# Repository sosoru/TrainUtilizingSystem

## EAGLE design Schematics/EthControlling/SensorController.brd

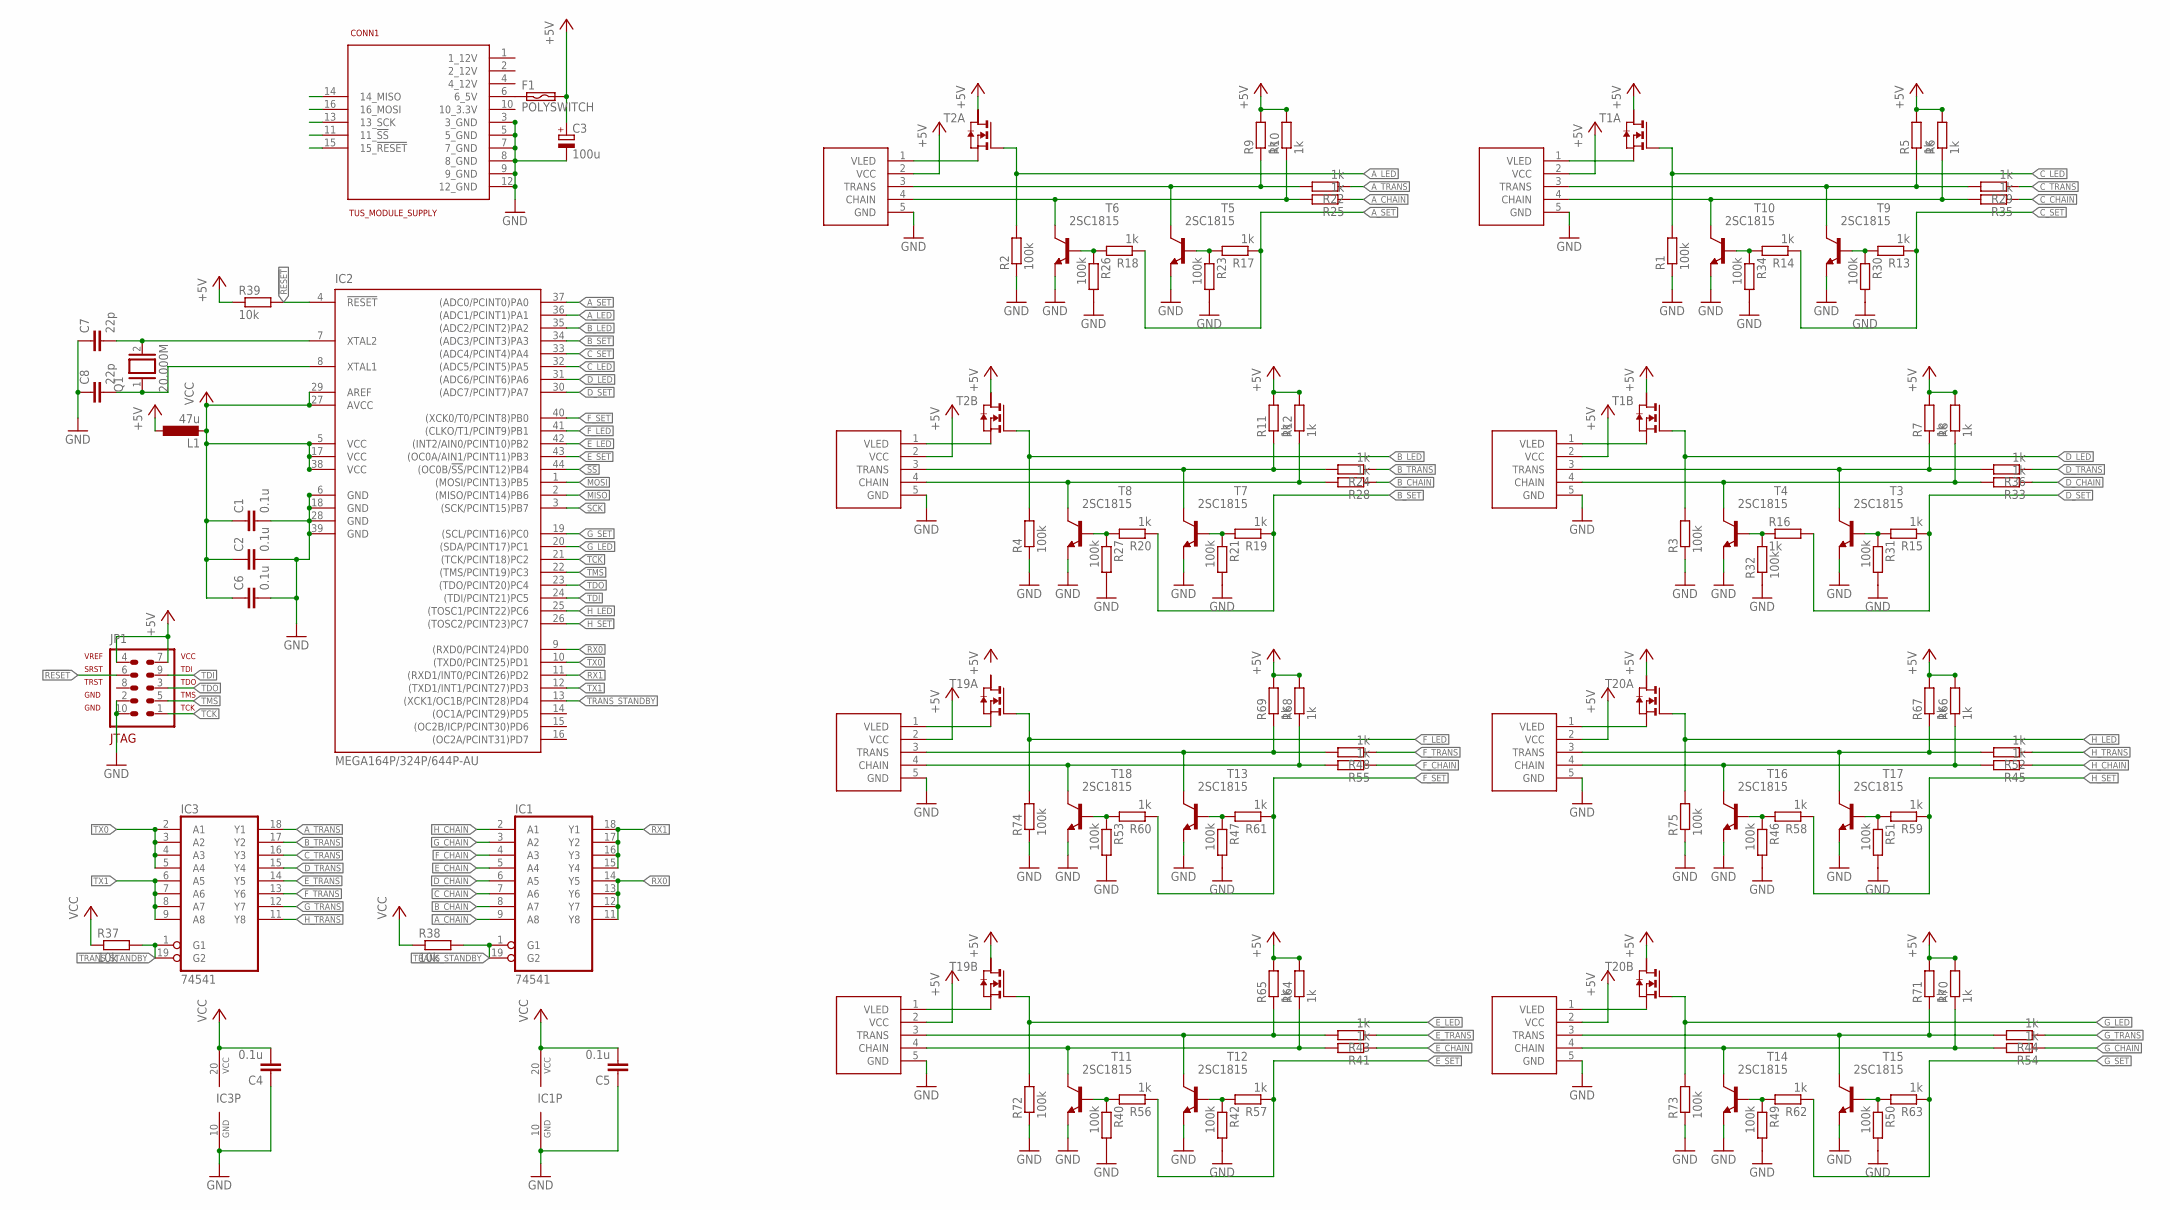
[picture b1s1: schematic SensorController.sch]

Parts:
A_OUT: SERIAL_SENSORXH; XH-5
B_OUT: SERIAL_SENSORXH; XH-5
C1, C2, C4, C5, C6: 0.1u; C1608
C3: 100u; E2,5-7
C7, C8: 22p; C1608
CONN1: TUS_MODULE_SUPPLY; 2X08
C_OUT: SERIAL_SENSORXH; XH-5
D_OUT: SERIAL_SENSORXH; XH-5
E_OUT: SERIAL_SENSORXH; XH-5
F1: POLYSWITCH; 0207/2V
F_OUT: SERIAL_SENSORXH; XH-5
G_OUT: SERIAL_SENSORXH; XH-5
H_OUT: SERIAL_SENSORXH; XH-5
IC1, IC3: 74541; SSOP20
IC2: MEGA164P/324P/644P-AU; TQFP44
JP1: AVR-JTAG-10
L1: 47u; L1812
Q1: 20.000M; QS
R1, R2, R3, R4, R21, R23, R26, R27, R30, R31, R32, R34, R40, R42, R46, R47, R49, R50, R51, R53, R72, R73, R74, R75: 100k; R0603
R5, R6, R7, R8, R9, R10, R11, R12, R13, R14, R15, R16, R17, R18, R19, R20, R22, R24, R25, R28, R29, R33, R35, R36, R41, R43, R44, R45, R48, R52, R54, R55, R56, R57, R58, R59, R60, R61, R62, R63, R64, R65, R66, R67, R68, R69, R70, R71: 1k; R0603
R37, R38, R39: 10k; R0603
T1, T2, T19, T20: NMOS2SO8; SO8
T3, T4, T5, T6, T7, T8, T9, T10, T11, T12, T13, T14, T15, T16, T17, T18: 2SC1815; TO92-ECB

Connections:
!RESET: CONN1.15 (15_!RESET), IC2.4 (!RESET), JP1.6, R39.2
!SS: CONN1.11 (11_!SS), IC2.44 ((OC0B/!SS!/PCINT12)PB4)
+5V: A_OUT.2 (VCC), B_OUT.2 (VCC), C3.+, C_OUT.2 (VCC), D_OUT.2 (VCC), E_OUT.2 (VCC), F1.2, F_OUT.2 (VCC), G_OUT.2 (VCC), H_OUT.2 (VCC), JP1.4, JP1.7, L1.1, R5.2, R6.2, R7.2, R8.2, R9.2, R10.2, R11.2, R12.2, R39.1, R64.2, R65.2, R66.2, R67.2, R68.2, R69.2, R70.2, R71.2, T1.6 (D), T1.8 (D), T2.6 (D), T2.8 (D), T19.6 (D), T20.6 (D), T20.8 (D)
A_CHAIN: IC1.9 (A8), R25.1
A_LED: IC2.36 ((ADC1/PCINT1)PA1), R2.2, T2.2 (G)
A_SET: IC2.37 ((ADC0/PCINT0)PA0), R17.1, R18.1
A_TRANS: IC3.18 (Y1), R22.1
B_CHAIN: IC1.8 (A7), R28.1
B_LED: IC2.35 ((ADC2/PCINT2)PA2), R4.2, T2.4 (G)
B_SET: IC2.34 ((ADC3/PCINT3)PA3), R19.1, R20.1
B_TRANS: IC3.17 (Y2), R24.1
C_CHAIN: IC1.7 (A6), R35.1
C_LED: IC2.32 ((ADC5/PCINT5)PA5), R1.2, T1.2 (G)
C_SET: IC2.33 ((ADC4/PCINT4)PA4), R13.1, R14.1
C_TRANS: IC3.16 (Y3), R29.1
D_CHAIN: IC1.6 (A5), R33.1
D_LED: IC2.31 ((ADC6/PCINT6)PA6), R3.2, T1.4 (G)
D_SET: IC2.30 ((ADC7/PCINT7)PA7), R15.1, R16.2
D_TRANS: IC3.15 (Y4), R36.1
E_CHAIN: IC1.5 (A4), R41.1
E_LED: IC2.42 ((INT2/AIN0/PCINT10)PB2), R72.2, T19.4 (G)
E_SET: IC2.43 ((OC0A/AIN1/PCINT11)PB3), R56.1, R57.1
E_TRANS: IC3.14 (Y5), R43.1
F_CHAIN: IC1.4 (A3), R55.1
F_LED: IC2.41 ((CLKO/T1/PCINT9)PB1), R74.2, T19.2 (G)
F_SET: IC2.40 ((XCK0/T0/PCINT8)PB0), R60.1, R61.1
F_TRANS: IC3.13 (Y6), R48.1
GND: A_OUT.5 (GND), B_OUT.5 (GND), C1.2, C2.2, C3.-, C4.1, C5.1, C6.2, C7.1, C8.1, CONN1.3 (3_GND), CONN1.5 (5_GND), CONN1.7 (7_GND), CONN1.8 (8_GND), CONN1.9 (9_GND), CONN1.12 (12_GND), C_OUT.5 (GND), D_OUT.5 (GND), E_OUT.5 (GND), F_OUT.5 (GND), G_OUT.5 (GND), H_OUT.5 (GND), IC1.10 (GND), IC2.6 (GND), IC2.18 (GND), IC2.28 (GND), IC2.39 (GND), IC3.10 (GND), JP1.2, JP1.10, R1.1, R2.1, R3.1, R4.1, R21.2, R23.2, R26.2, R27.2, R30.2, R31.2, R32.1, R34.2, R40.2, R42.2, R46.2, R47.2, R49.2, R50.2, R51.2, R53.2, R72.1, R73.1, R74.1, R75.1, T3.E, T4.E, T5.E, T6.E, T7.E, T8.E, T9.E, T10.E, T11.E, T12.E, T13.E, T14.E, T15.E, T16.E, T17.E, T18.E
G_CHAIN: IC1.3 (A2), R54.1
G_LED: IC2.20 ((SDA/PCINT17)PC1), R73.2, T20.4 (G)
G_SET: IC2.19 ((SCL/PCINT16)PC0), R62.1, R63.1
G_TRANS: IC3.12 (Y7), R44.1
H_CHAIN: IC1.2 (A1), R45.1
H_LED: IC2.25 ((TOSC1/PCINT22)PC6), R75.2, T20.2 (G)
H_SET: IC2.26 ((TOSC2/PCINT23)PC7), R58.1, R59.1
H_TRANS: IC3.11 (Y8), R52.1
MISO: CONN1.14 (14_MISO), IC2.2 ((MISO/PCINT14)PB6)
MOSI: CONN1.16 (16_MOSI), IC2.1 ((MOSI/PCINT13)PB5)
unnamed: A_OUT.1 (VLED), T2.1 (S)
unnamed: C8.2, IC2.8 (XTAL1), Q1.1
unnamed: R17.2, R23.1, T5.B
unnamed: C7.2, IC2.7 (XTAL2), Q1.2
unnamed: R18.2, R26.1, T6.B
unnamed: B_OUT.1 (VLED), T2.3 (S)
unnamed: R19.2, R21.1, T7.B
unnamed: R20.2, R27.1, T8.B
unnamed: F_OUT.1 (VLED), T19.1 (S)
unnamed: R47.1, R61.2, T13.B
unnamed: R53.1, R60.2, T18.B
unnamed: E_OUT.1 (VLED), T19.3 (S)
unnamed: R42.1, R57.2, T12.B
unnamed: R40.1, R56.2, T11.B
unnamed: C_OUT.1 (VLED), T1.1 (S)
unnamed: R13.2, R30.1, T9.B
unnamed: R14.2, R34.1, T10.B
unnamed: D_OUT.1 (VLED), T1.3 (S)
unnamed: R15.2, R31.1, T3.B
unnamed: R16.1, R32.2, T4.B
unnamed: H_OUT.1 (VLED), T20.1 (S)
unnamed: R51.1, R59.2, T17.B
unnamed: R46.1, R58.2, T16.B
unnamed: G_OUT.1 (VLED), T20.3 (S)
unnamed: R50.1, R63.2, T15.B
unnamed: R49.1, R62.2, T14.B
unnamed: CONN1.6 (6_5V), F1.1
unnamed: A_OUT.3 (TRANS), R9.1, R22.2, T5.C
unnamed: B_OUT.3 (TRANS), R11.1, R24.2, T7.C
unnamed: C_OUT.3 (TRANS), R5.1, R29.2, T9.C
unnamed: D_OUT.3 (TRANS), R7.1, R36.2, T3.C
unnamed: F_OUT.3 (TRANS), R48.2, R69.1, T13.C
unnamed: H_OUT.3 (TRANS), R52.2, R67.1, T17.C
unnamed: E_OUT.3 (TRANS), R43.2, R65.1, T12.C
unnamed: G_OUT.3 (TRANS), R44.2, R71.1, T15.C
unnamed: A_OUT.4 (CHAIN), R10.1, R25.2, T6.C
unnamed: B_OUT.4 (CHAIN), R12.1, R28.2, T8.C
unnamed: F_OUT.4 (CHAIN), R55.2, R68.1, T18.C
unnamed: E_OUT.4 (CHAIN), R41.2, R64.1, T11.C
unnamed: D_OUT.4 (CHAIN), R8.1, R33.2, T4.C
unnamed: C_OUT.4 (CHAIN), R6.1, R35.2, T10.C
unnamed: H_OUT.4 (CHAIN), R45.2, R66.1, T16.C
unnamed: G_OUT.4 (CHAIN), R54.2, R70.1, T14.C
RX0: IC1.11 (Y8), IC1.12 (Y7), IC1.13 (Y6), IC1.14 (Y5), IC2.9 ((RXD0/PCINT24)PD0)
RX1: IC1.15 (Y4), IC1.16 (Y3), IC1.17 (Y2), IC1.18 (Y1), IC2.11 ((RXD1/INT0/PCINT26)PD2)
SCK: CONN1.13 (13_SCK), IC2.3 ((SCK/PCINT15)PB7)
TCK: IC2.21 ((TCK/PCINT18)PC2), JP1.1
TDI: IC2.24 ((TDI/PCINT21)PC5), JP1.9
TDO: IC2.23 ((TDO/PCINT20)PC4), JP1.3
TMS: IC2.22 ((TMS/PCINT19)PC3), JP1.5
TRANS_STANDBY: IC1.1 (G1), IC1.19 (G2), IC2.13 ((XCK1/OC1B/PCINT28)PD4), IC3.1 (G1), IC3.19 (G2), R37.2, R38.2
TX0: IC2.10 ((TXD0/PCINT25)PD1), IC3.2 (A1), IC3.3 (A2), IC3.4 (A3), IC3.5 (A4)
TX1: IC2.12 ((TXD1/INT1/PCINT27)PD3), IC3.6 (A5), IC3.7 (A6), IC3.8 (A7), IC3.9 (A8)
VCC: C1.1, C2.1, C4.2, C5.2, C6.1, IC1.20 (VCC), IC2.5 (VCC), IC2.17 (VCC), IC2.27 (AVCC), IC2.29 (AREF), IC2.38 (VCC), IC3.20 (VCC), L1.2, R37.1, R38.1

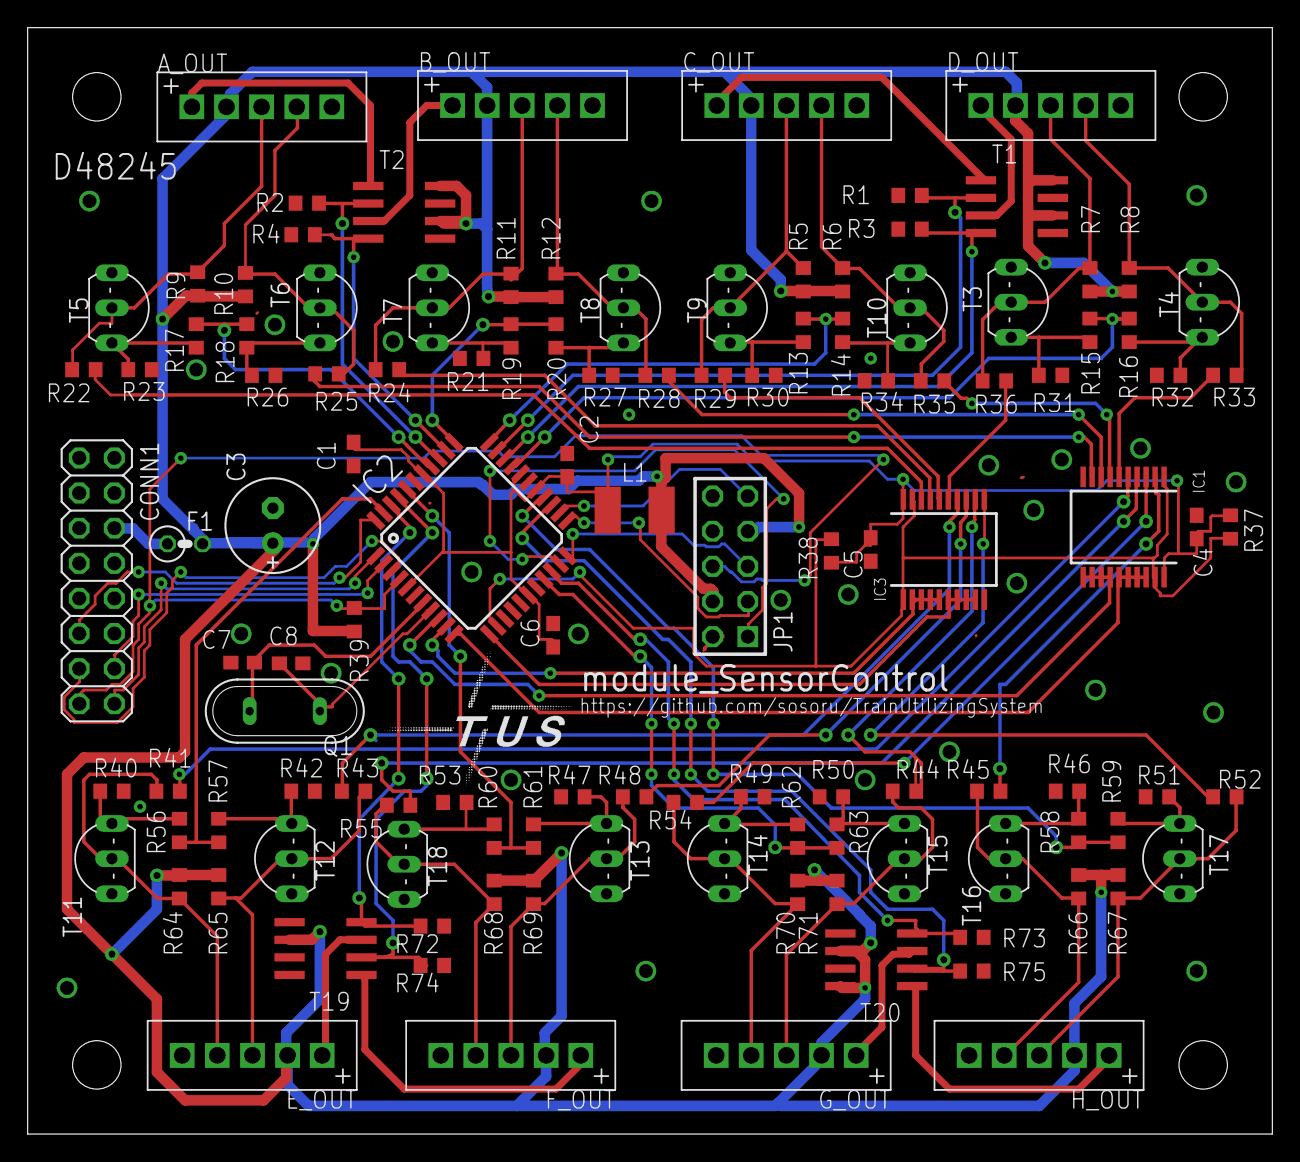
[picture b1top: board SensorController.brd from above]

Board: 2 copper layers, 90.0 x 80.0 mm, 119 parts (0 on the bottom side), 92 nets.

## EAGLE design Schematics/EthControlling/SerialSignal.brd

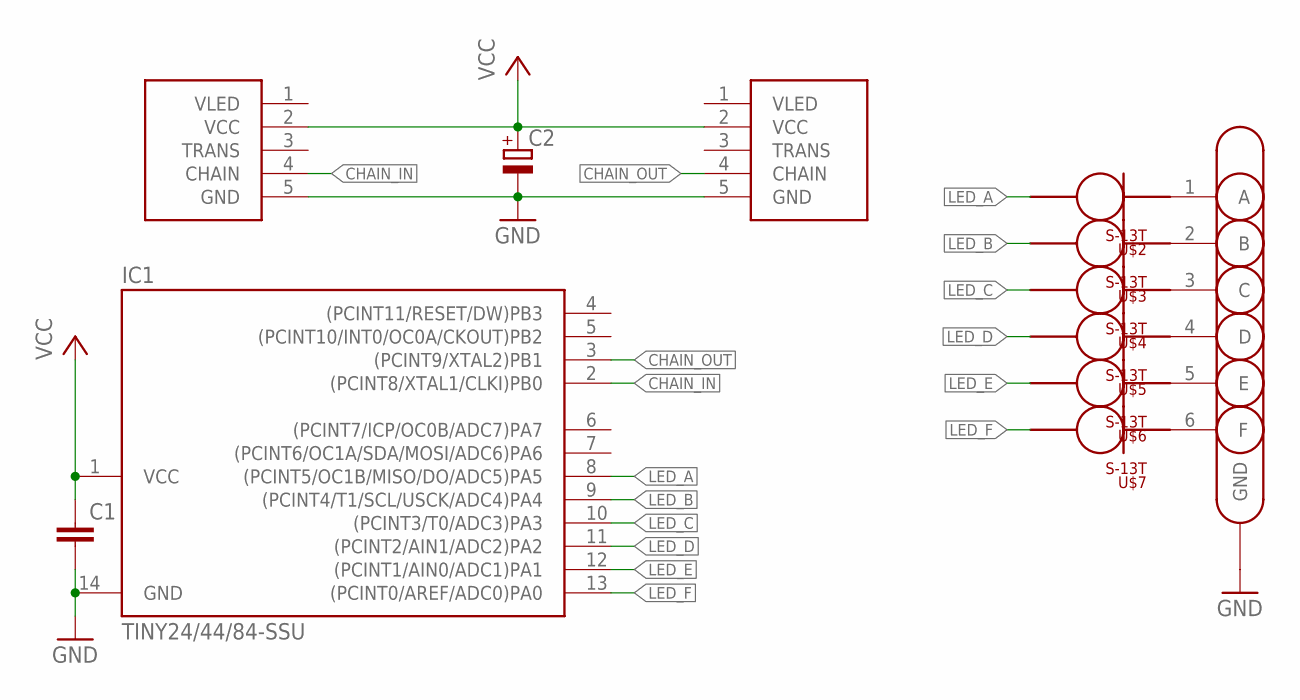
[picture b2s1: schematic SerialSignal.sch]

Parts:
C1: C-EUC0603; C0603
C2: CPOL-EUSMCC; SMC_C
IC1: TINY24/44/84-SSU; SOIC14
SMD1, SMD2: SERIAL_SENSOR; SERIAL_4
U$1: SIGNAL_CONNECTOR; SIGNEL_CONNECTOR
U$2, U$3, U$4, U$5, U$6, U$7: S-13T; S-1*3T

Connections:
CHAIN_IN: IC1.2 ((PCINT8/XTAL1/CLKI)PB0), SMD1.4 (CHAIN)
CHAIN_OUT: IC1.3 ((PCINT9/XTAL2)PB1), SMD2.4 (CHAIN)
GND: C1.2, C2.-, IC1.14 (GND), SMD1.5 (GND), SMD2.5 (GND), U$1.GND
LED_A: IC1.8 ((PCINT5/OC1B/MISO/DO/ADC5)PA5), U$2.A
LED_B: IC1.9 ((PCINT4/T1/SCL/USCK/ADC4)PA4), U$3.A
LED_C: IC1.10 ((PCINT3/T0/ADC3)PA3), U$4.A
LED_D: IC1.11 ((PCINT2/AIN1/ADC2)PA2), U$5.A
LED_E: IC1.12 ((PCINT1/AIN0/ADC1)PA1), U$6.A
LED_F: IC1.13 ((PCINT0/AREF/ADC0)PA0), U$7.A
unnamed: U$1.1 (A), U$2.C
unnamed: U$1.2 (B), U$3.C
unnamed: U$1.3 (C), U$4.C
unnamed: U$1.4 (D), U$5.C
unnamed: U$1.5 (E), U$6.C
unnamed: U$1.6 (F), U$7.C
VCC: C1.1, C2.+, IC1.1 (VCC), SMD1.2 (VCC), SMD2.2 (VCC)

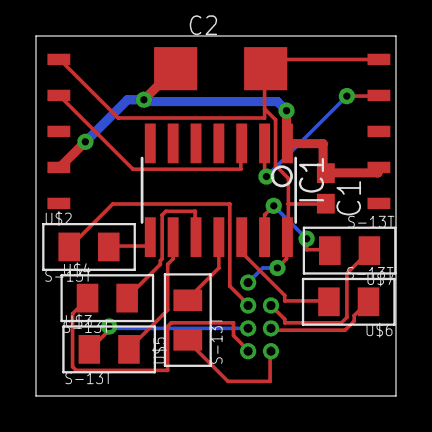
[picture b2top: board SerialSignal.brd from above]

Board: 2 copper layers, 20.0 x 20.0 mm, 12 parts (0 on the bottom side), 16 nets.

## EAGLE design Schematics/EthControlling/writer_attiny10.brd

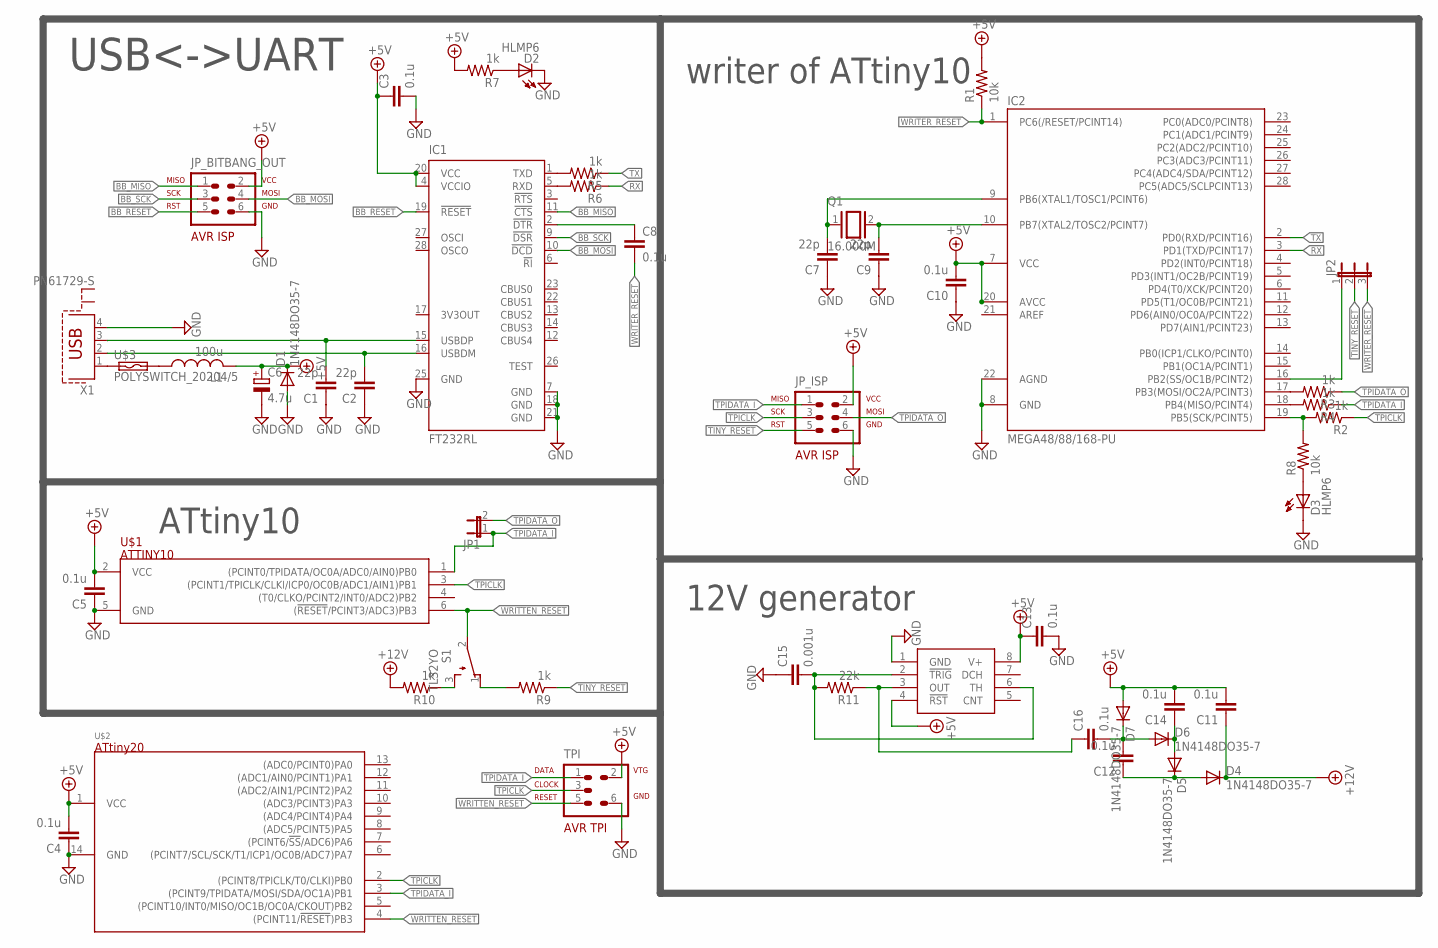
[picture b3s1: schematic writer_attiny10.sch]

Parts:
C1, C2, C7, C9: 22p; C0603
C3, C4, C5, C8, C10, C11, C12, C13, C14, C16: 0.1u; C0603
C6: 4.7u; CT3216
C15: 0.001u; C0603
D1, D4, D5, D6, D7: 1N4148DO35-7; DO35-7
D2: HLMP6; MPN HLMP-6500
D3: HLMP6
IC1: FT232RL; SSOP28
IC2: MEGA48/88/168-PU; DIL28-3
IC3: LMC555; DIL08
JP1: JP1E; JP1
JP2: JP2E; JP2
JP_BITBANG_OUT: AVR-ISP-6VERT; AVR-ISP-6
JP_ISP: AVR-ISP-6VERT; AVR-ISP-6
L1: 100u; 0207/10
Q1: 16.000M; QS
R1, R8: 10k; R0603
R2, R3, R4, R5, R6, R7, R9, R10: 1k; R0603
R11: 22k; R0603
S1: TL32YO; TL3XYO
TPI: AVR-TPIVERT; AVR-ISP-6
U$1: ATTINY10; SOT-23
U$2: ATTINY20; SOIC14
U$3: POLYSWITCH_20204/5; 0204/5
X1: PN61729-S

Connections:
+5V: C3.1, C4.2, C5.2, C6.+, C10.2, C11.2, C13.1, C14.2, D1.C, D7.A, IC1.4 (VCCIO), IC1.20 (VCC), IC2.7 (VCC), IC2.20 (AVCC), IC3.4 (!RST), IC3.8 (V+), JP_BITBANG_OUT.2, JP_ISP.2, L1.2, R1.2, R7.2, TPI.2, U$1.2 (VCC), U$2.1 (VCC)
+12V: C11.1, D4.C, R10.2
BB_MISO: IC1.11 (!CTS), JP_BITBANG_OUT.1
BB_MOSI: IC1.10 (!DCD), JP_BITBANG_OUT.4
BB_RESET: IC1.19 (!RESET), JP_BITBANG_OUT.5
BB_SCK: IC1.9 (!DSR), JP_BITBANG_OUT.3
GND: C1.1, C2.1, C3.2, C4.1, C5.1, C6.-, C7.1, C9.1, C10.1, C13.2, C15.1, D1.A, D2.K, D3.K, IC1.7 (GND), IC1.18 (GND), IC1.21 (GND), IC1.25 (GND), IC2.8 (GND), IC2.22 (AGND), IC3.1 (GND), JP_BITBANG_OUT.6, JP_ISP.6, TPI.6, U$1.5 (GND), U$2.14 (GND), X1.4
unnamed: C2.2, IC1.16 (USBDM), X1.2
unnamed: C1.2, IC1.15 (USBDP), X1.3
unnamed: U$3.1, X1.1
unnamed: C7.2, IC2.9 (PB6(XTAL1/TOSC1/PCINT6)), Q1.1
unnamed: C9.2, IC2.10 (PB7(XTAL2/TOSC2/PCINT7)), Q1.2
unnamed: IC2.18 (PB4(MISO/PCINT4)), R4.2
unnamed: D2.A, R7.1
unnamed: D3.A, R8.1
unnamed: IC1.5 (RXD), R6.2
unnamed: C12.2, C16.2, D6.A, D7.C
unnamed: IC1.1 (TXD), R5.2
unnamed: C15.2, IC3.2 (!TRIG), IC3.6 (TH), R11.2
unnamed: C16.1, IC3.3 (OUT), R11.1
unnamed: C14.1, D5.A, D6.C
unnamed: C12.1, D4.A, D5.C
unnamed: R10.1, S1.3 (S)
unnamed: R9.2, S1.1 (O)
unnamed: L1.1, U$3.2
unnamed: IC2.17 (PB3(MOSI/OC2A/PCINT3)), R3.2
unnamed: IC2.16 (PB2(SS/OC1B/PCINT2)), JP2.1
unnamed: C8.1, IC1.2 (!DTR)
unnamed: IC2.19 (PB5(SCK/PCINT5)), R2.2, R8.2
RX: IC2.3 (PD1(TXD/PCINT17)), R6.1
TINY_RESET: JP2.2, JP_ISP.5, R9.1
TPICLK: JP_ISP.3, R2.1, TPI.3, U$1.3 ((PCINT1/TPICLK/CLKI/ICP0/OC0B/ADC1/AIN1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), U$2.2 ((PCINT8/TPICLK/T0/CLKI)PB0)
TPIDATA_I: JP1.1, JP_ISP.1, R4.1, TPI.1, U$1.1 ((PCINT0/TPIDATA/OC0A/ADC0/AIN0)PB0), U$2.3 ((PCINT9/TPIDATA/MOSI/SDA/OC1A)PB1)
TPIDATA_O: JP1.2, JP_ISP.4, R3.1
TX: IC2.2 (PD0(RXD/PCINT16)), R5.1
WRITER_RESET: C8.2, IC2.1 (PC6(/RESET/PCINT14)), JP2.3, R1.1
WRITTEN_RESET: S1.2, TPI.5, U$1.6 ((!RESET!/PCINT3/ADC3)PB3), U$2.4 ((PCINT11/!RESET!)PB3)

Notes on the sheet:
USB<->UART
writer of ATtiny10
ATtiny10
12V generator

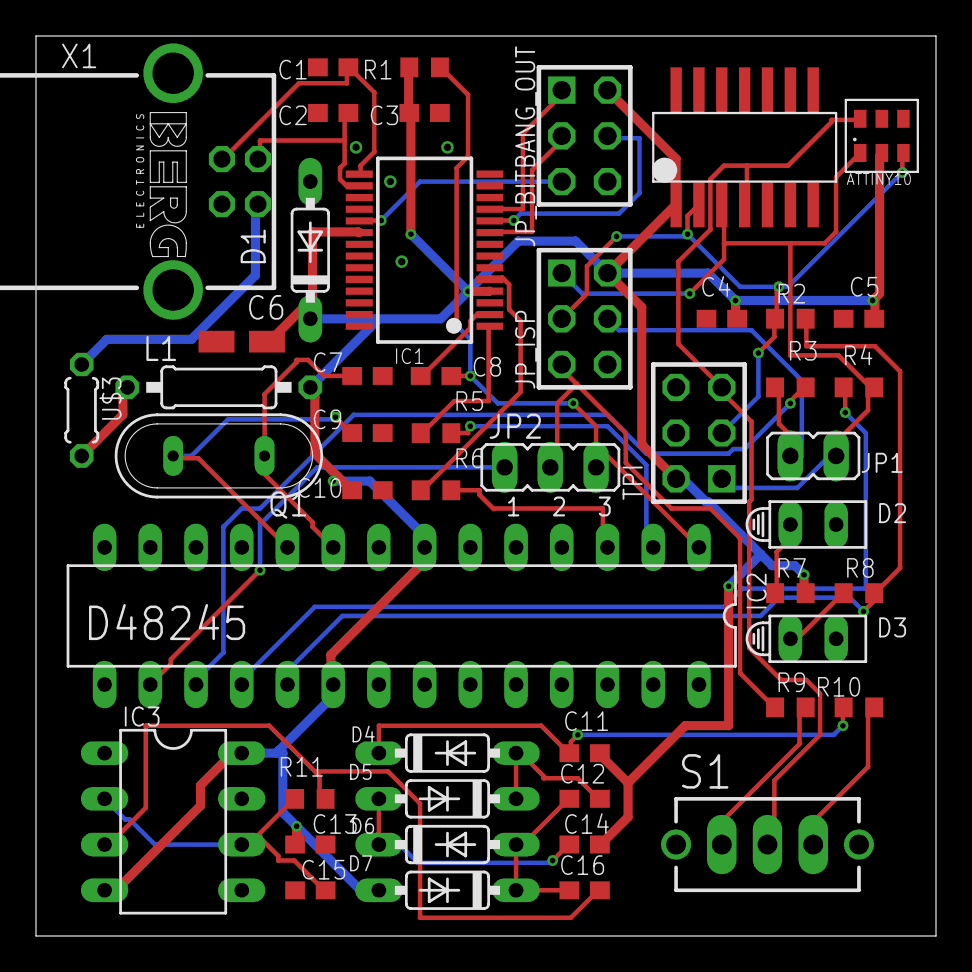
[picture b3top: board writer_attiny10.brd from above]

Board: 2 copper layers, 50.0 x 50.0 mm, 49 parts (0 on the bottom side), 37 nets.

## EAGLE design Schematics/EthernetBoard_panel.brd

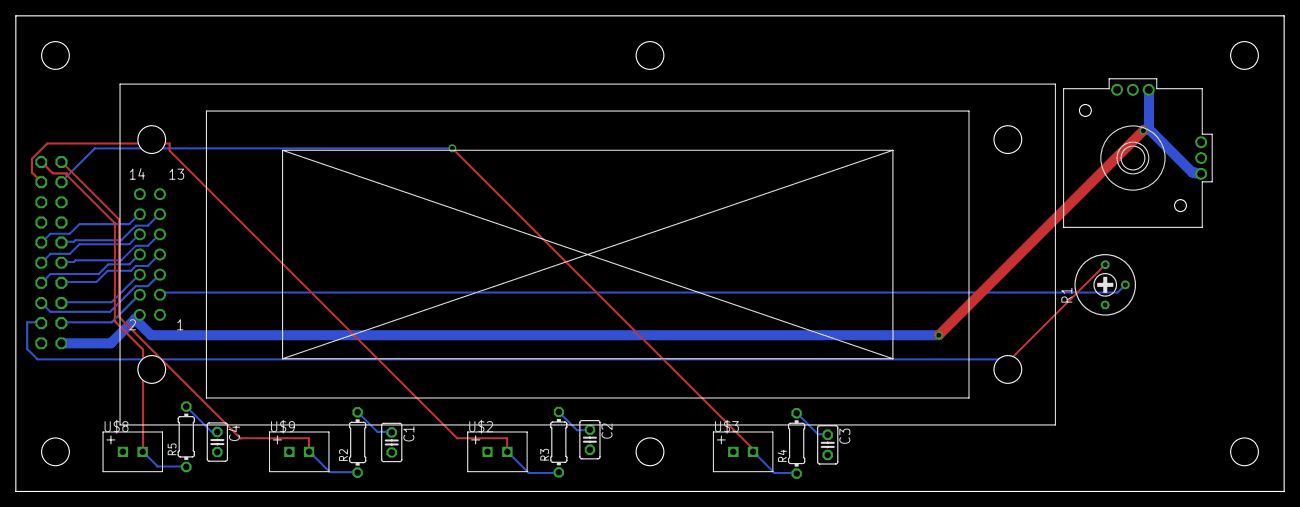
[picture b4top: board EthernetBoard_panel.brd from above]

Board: 2 copper layers, 160.0 x 60.0 mm, 16 parts (1 on the bottom side), 25 nets.

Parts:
C1, C2, C3, C4: 1u; C025-025X050
JP1: 2X10
R1: 10k; RTRIM3339P
R2, R3, R4, R5: 4.7k; 0204/7
U$1: SC2004
U$2, U$3, U$8, U$9: XH-2
U$4: JT8P-3.2T-B10K-1-16Y

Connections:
+5V: JP1.2, U$1.2, U$4.1, U$4.'1
GND: C1.2, C2.2, C3.2, C4.2, JP1.1, R1.1, U$1.1, U$2.P$1, U$3.P$1, U$4.3, U$4.'3, U$8.P$1, U$9.P$1
LCD_DB0: JP1.8, U$1.7
LCD_DB1: JP1.7, U$1.8
LCD_DB2: JP1.10, U$1.9
LCD_DB3: JP1.9, U$1.10
LCD_DB4: JP1.12, U$1.11
LCD_DB5: JP1.11, U$1.12
LCD_DB6: JP1.14, U$1.13
LCD_DB7: JP1.13, U$1.14
LCD_E: JP1.6, U$1.6
LCD_RS: JP1.4, U$1.4
LCD_RW: JP1.5, U$1.5
LCD_SW1: JP1.19, R5.1, U$8.P$2
LCD_SW2: JP1.20, R2.1, U$9.P$2
LCD_SW3: JP1.17, R3.1, U$2.P$2
LCD_SW4: JP1.18, R4.1, U$3.P$2
LCD_SW5: JP1.15, U$4.2
LCD_SW6: JP1.16, U$4.'2
LCD_VO: R1.2, U$1.3
unnamed: JP1.3, R1.3
unnamed: C1.1, R2.2
unnamed: C2.1, R3.2
unnamed: C3.1, R4.2
unnamed: C4.1, R5.2

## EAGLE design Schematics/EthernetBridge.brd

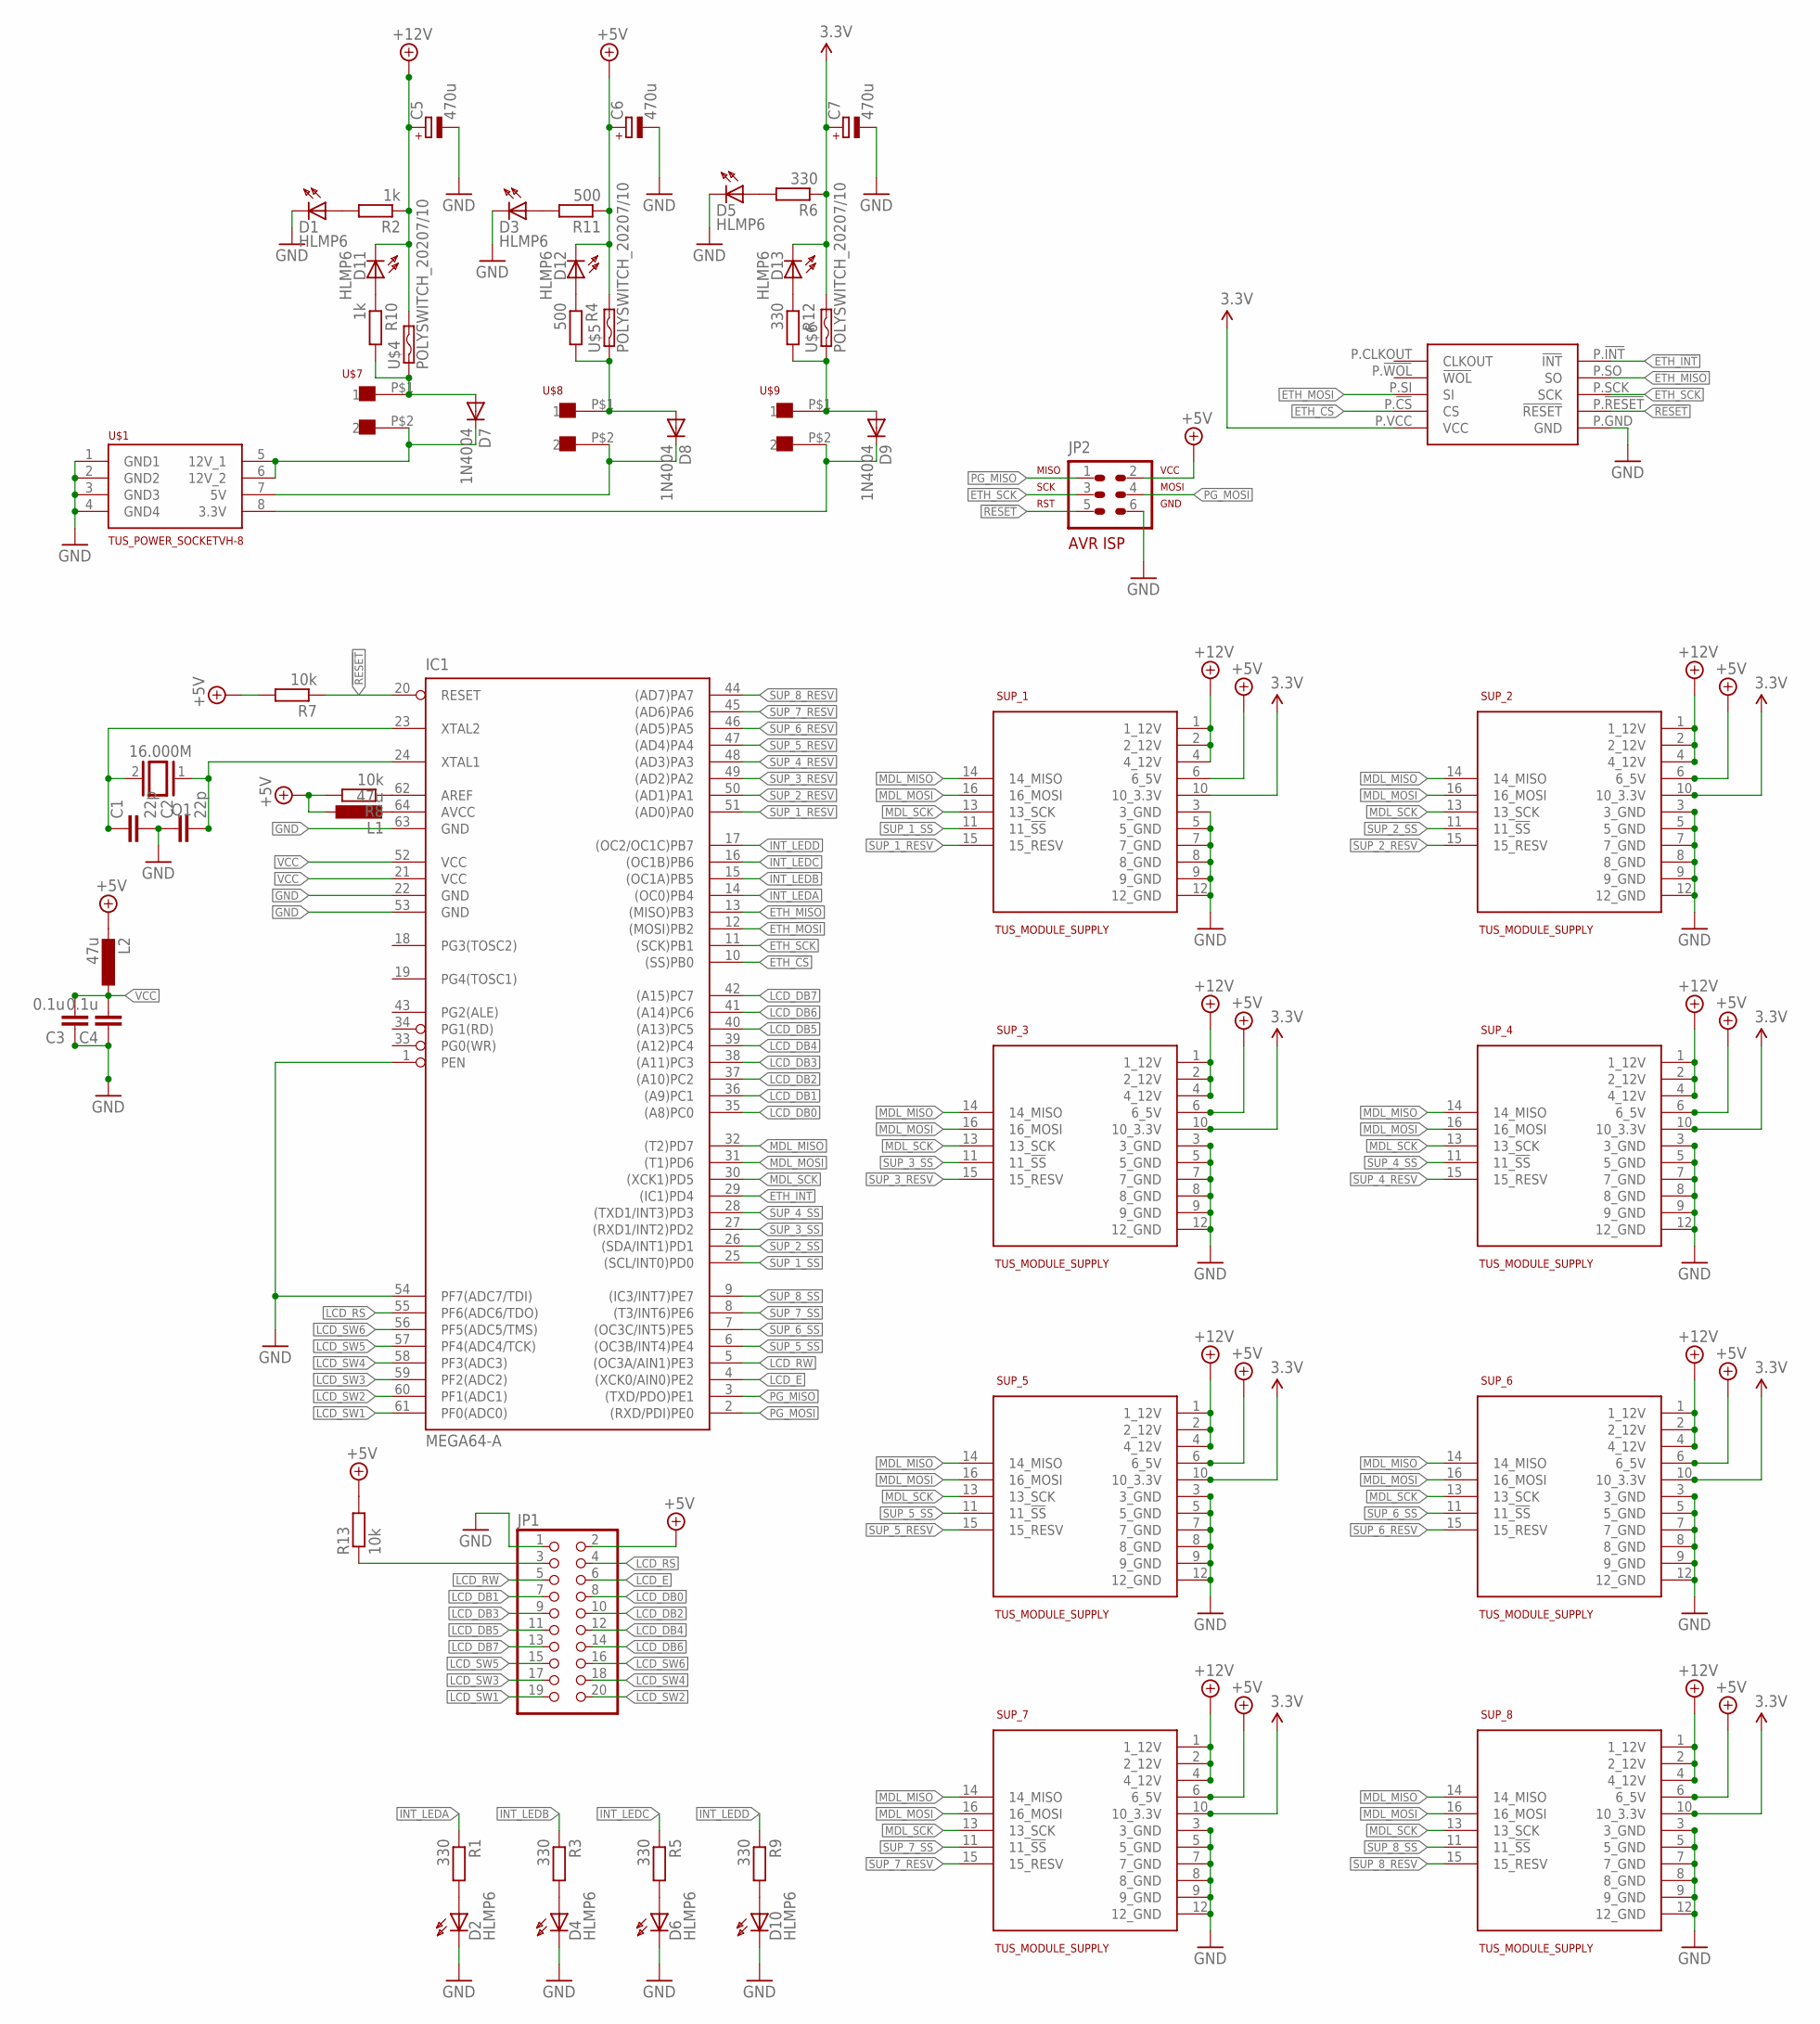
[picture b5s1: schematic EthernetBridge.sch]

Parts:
C1, C2: 22p; C2.5-3
C3, C4: 0.1u; C2.5-3
C5, C6, C7: 470u; E5-10,5
D1, D2, D3, D4, D5, D6, D10, D11, D12, D13: HLMP6
D7, D8, D9: 1N4004; DO41-10
IC1: MEGA64-A; TQFP64
JP1: PINHD-2X10; 2X10
JP2: AVR-ISP-6VERT; AVR-ISP-6
L1, L2: 47u; 0204/7
Q1: 16.000M; QS
R1, R3, R5, R6, R9, R12: 330; 0204/7
R2, R10: 1k; 0204/7
R4, R11: 500; 0204/7
R7, R8, R13: 10k; 0204/7
SUP_1, SUP_2, SUP_3, SUP_4, SUP_5, SUP_6, SUP_7, SUP_8: TUS_MODULE_SUPPLY; 2X08
U$1: TUS_POWER_SOCKETVH-8; VH_8
U$2: AITENDO_ENC28J60
U$4, U$5, U$6: POLYSWITCH_20207/10; 0207/10
U$7, U$8, U$9: VH-2

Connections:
3.3V: C7.+, D13.K, R6.1, SUP_1.10 (10_3.3V), SUP_2.10 (10_3.3V), SUP_3.10 (10_3.3V), SUP_4.10 (10_3.3V), SUP_5.10 (10_3.3V), SUP_6.10 (10_3.3V), SUP_7.10 (10_3.3V), SUP_8.10 (10_3.3V), U$2.P.VCC (VCC), U$6.2
!RESET: IC1.20 (RESET), JP2.5, R7.1, U$2.P.!RESET (!RESET)
+5V: C6.+, D12.K, JP1.2, JP2.2, L1.1, L2.2, R7.2, R8.2, R11.1, R13.2, SUP_1.6 (6_5V), SUP_2.6 (6_5V), SUP_3.6 (6_5V), SUP_4.6 (6_5V), SUP_5.6 (6_5V), SUP_6.6 (6_5V), SUP_7.6 (6_5V), SUP_8.6 (6_5V), U$5.2
+12V: C5.+, D11.K, R2.1, SUP_1.1 (1_12V), SUP_1.2 (2_12V), SUP_1.4 (4_12V), SUP_2.1 (1_12V), SUP_2.2 (2_12V), SUP_2.4 (4_12V), SUP_3.1 (1_12V), SUP_3.2 (2_12V), SUP_3.4 (4_12V), SUP_4.1 (1_12V), SUP_4.2 (2_12V), SUP_4.4 (4_12V), SUP_5.1 (1_12V), SUP_5.2 (2_12V), SUP_5.4 (4_12V), SUP_6.1 (1_12V), SUP_6.2 (2_12V), SUP_6.4 (4_12V), SUP_7.1 (1_12V), SUP_7.2 (2_12V), SUP_7.4 (4_12V), SUP_8.1 (1_12V), SUP_8.2 (2_12V), SUP_8.4 (4_12V), U$4.2
ETH_!CS: IC1.10 ((SS)PB0), U$2.P.!CS (CS)
ETH_!INT: IC1.29 ((IC1)PD4), U$2.P.!INT (!INT)
ETH_MISO: IC1.13 ((MISO)PB3), U$2.P.SO (SO)
ETH_MOSI: IC1.12 ((MOSI)PB2), U$2.P.SI (SI)
ETH_SCK: IC1.11 ((SCK)PB1), JP2.3, U$2.P.SCK (SCK)
GND: C1.2, C2.1, C3.1, C4.1, C5.-, C6.-, C7.-, D1.K, D2.K, D3.K, D4.K, D5.K, D6.K, D10.K, IC1.1 (PEN), IC1.22 (GND), IC1.53 (GND), IC1.54 (PF7(ADC7/TDI)), IC1.63 (GND), JP1.1, JP2.6, SUP_1.3 (3_GND), SUP_1.5 (5_GND), SUP_1.7 (7_GND), SUP_1.8 (8_GND), SUP_1.9 (9_GND), SUP_1.12 (12_GND), SUP_2.3 (3_GND), SUP_2.5 (5_GND), SUP_2.7 (7_GND), SUP_2.8 (8_GND), SUP_2.9 (9_GND), SUP_2.12 (12_GND), SUP_3.3 (3_GND), SUP_3.5 (5_GND), SUP_3.7 (7_GND), SUP_3.8 (8_GND), SUP_3.9 (9_GND), SUP_3.12 (12_GND), SUP_4.3 (3_GND), SUP_4.5 (5_GND), SUP_4.7 (7_GND), SUP_4.8 (8_GND), SUP_4.9 (9_GND), SUP_4.12 (12_GND), SUP_5.3 (3_GND), SUP_5.5 (5_GND), SUP_5.7 (7_GND), SUP_5.8 (8_GND), SUP_5.9 (9_GND), SUP_5.12 (12_GND), SUP_6.3 (3_GND), SUP_6.5 (5_GND), SUP_6.7 (7_GND), SUP_6.8 (8_GND), SUP_6.9 (9_GND), SUP_6.12 (12_GND), SUP_7.3 (3_GND), SUP_7.5 (5_GND), SUP_7.7 (7_GND), SUP_7.8 (8_GND), SUP_7.9 (9_GND), SUP_7.12 (12_GND), SUP_8.3 (3_GND), SUP_8.5 (5_GND), SUP_8.7 (7_GND), SUP_8.8 (8_GND), SUP_8.9 (9_GND), SUP_8.12 (12_GND), U$1.1 (GND1), U$1.2 (GND2), U$1.3 (GND3), U$1.4 (GND4), U$2.P.GND (GND)
INT_LEDA: IC1.14 ((OC0)PB4), R1.1
INT_LEDB: IC1.15 ((OC1A)PB5), R3.1
INT_LEDC: IC1.16 ((OC1B)PB6), R5.1
INT_LEDD: IC1.17 ((OC2/OC1C)PB7), R9.1
LCD_DB0: IC1.35 ((A8)PC0), JP1.8
LCD_DB1: IC1.36 ((A9)PC1), JP1.7
LCD_DB2: IC1.37 ((A10)PC2), JP1.10
LCD_DB3: IC1.38 ((A11)PC3), JP1.9
LCD_DB4: IC1.39 ((A12)PC4), JP1.12
LCD_DB5: IC1.40 ((A13)PC5), JP1.11
LCD_DB6: IC1.41 ((A14)PC6), JP1.14
LCD_DB7: IC1.42 ((A15)PC7), JP1.13
LCD_E: IC1.4 ((XCK0/AIN0)PE2), JP1.6
LCD_RS: IC1.55 (PF6(ADC6/TDO)), JP1.4
LCD_RW: IC1.5 ((OC3A/AIN1)PE3), JP1.5
LCD_SW1: IC1.61 (PF0(ADC0)), JP1.19
LCD_SW2: IC1.60 (PF1(ADC1)), JP1.20
LCD_SW3: IC1.59 (PF2(ADC2)), JP1.17
LCD_SW4: IC1.58 (PF3(ADC3)), JP1.18
LCD_SW5: IC1.57 (PF4(ADC4/TCK)), JP1.15
LCD_SW6: IC1.56 (PF5(ADC5/TMS)), JP1.16
LCD_VO: JP1.3, R13.1
MDL_MISO: IC1.32 ((T2)PD7), SUP_1.14 (14_MISO), SUP_2.14 (14_MISO), SUP_3.14 (14_MISO), SUP_4.14 (14_MISO), SUP_5.14 (14_MISO), SUP_6.14 (14_MISO), SUP_7.14 (14_MISO), SUP_8.14 (14_MISO)
MDL_MOSI: IC1.31 ((T1)PD6), SUP_1.16 (16_MOSI), SUP_2.16 (16_MOSI), SUP_3.16 (16_MOSI), SUP_4.16 (16_MOSI), SUP_5.16 (16_MOSI), SUP_6.16 (16_MOSI), SUP_7.16 (16_MOSI), SUP_8.16 (16_MOSI)
MDL_SCK: IC1.30 ((XCK1)PD5), SUP_1.13 (13_SCK), SUP_2.13 (13_SCK), SUP_3.13 (13_SCK), SUP_4.13 (13_SCK), SUP_5.13 (13_SCK), SUP_6.13 (13_SCK), SUP_7.13 (13_SCK), SUP_8.13 (13_SCK)
unnamed: IC1.64 (AVCC), L1.2
unnamed: D1.A, R2.2
unnamed: D2.A, R1.2
unnamed: D4.A, R3.2
unnamed: D8.A, R4.2, U$5.1, U$8.P$1 (1)
unnamed: D9.C, U$1.8 (3.3V), U$9.P$2 (2)
unnamed: D6.A, R5.2
unnamed: D5.A, R6.2
unnamed: C2.2, IC1.24 (XTAL1), Q1.1
unnamed: D10.A, R9.2
unnamed: C1.1, IC1.23 (XTAL2), Q1.2
unnamed: IC1.62 (AREF), R8.1
unnamed: D7.A, R10.2, U$4.1, U$7.P$1 (1)
unnamed: D11.A, R10.1
unnamed: D3.A, R11.2
unnamed: D12.A, R4.1
unnamed: D13.A, R12.1
unnamed: D9.A, R12.2, U$6.1, U$9.P$1 (1)
unnamed: D7.C, U$1.5 (12V_1), U$1.6 (12V_2), U$7.P$2 (2)
unnamed: D8.C, U$1.7 (5V), U$8.P$2 (2)
PG_MISO: IC1.3 ((TXD/PDO)PE1), JP2.1
PG_MOSI: IC1.2 ((RXD/PDI)PE0), JP2.4
SUP_1_RESV: IC1.51 ((AD0)PA0), SUP_1.15 (15_RESV)
SUP_1_SS: IC1.25 ((SCL/INT0)PD0), SUP_1.11 (11_!SS)
SUP_2_RESV: IC1.50 ((AD1)PA1), SUP_2.15 (15_RESV)
SUP_2_SS: IC1.26 ((SDA/INT1)PD1), SUP_2.11 (11_!SS)
SUP_3_RESV: IC1.49 ((AD2)PA2), SUP_3.15 (15_RESV)
SUP_3_SS: IC1.27 ((RXD1/INT2)PD2), SUP_3.11 (11_!SS)
SUP_4_RESV: IC1.48 ((AD3)PA3), SUP_4.15 (15_RESV)
SUP_4_SS: IC1.28 ((TXD1/INT3)PD3), SUP_4.11 (11_!SS)
SUP_5_RESV: IC1.47 ((AD4)PA4), SUP_5.15 (15_RESV)
SUP_5_SS: IC1.6 ((OC3B/INT4)PE4), SUP_5.11 (11_!SS)
SUP_6_RESV: IC1.46 ((AD5)PA5), SUP_6.15 (15_RESV)
SUP_6_SS: IC1.7 ((OC3C/INT5)PE5), SUP_6.11 (11_!SS)
SUP_7_RESV: IC1.45 ((AD6)PA6), SUP_7.15 (15_RESV)
SUP_7_SS: IC1.8 ((T3/INT6)PE6), SUP_7.11 (11_!SS)
SUP_8_RESV: IC1.44 ((AD7)PA7), SUP_8.15 (15_RESV)
SUP_8_SS: IC1.9 ((IC3/INT7)PE7), SUP_8.11 (11_!SS)
VCC: C3.2, C4.2, IC1.21 (VCC), IC1.52 (VCC), L2.1
